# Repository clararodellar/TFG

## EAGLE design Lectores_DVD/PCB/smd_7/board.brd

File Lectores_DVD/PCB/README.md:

En esta carpeta están los archivos para poder hacer la PCB, tanto el archivo esquemático (.sch) como el archivo de la placa (.brd).

Estas placas están hechas para que la conexión de los componentes a Arduino sea más cómoda.

Los componentes tienen las siguientes librerías: 52793-xx70, siendo xx el número de pines que tiene el conector.

Todos estos conectores sirven para conectar los motores de los lectores de DVD y hacemos la conexión a Arduino para poder comprobarlos.

La forma en que están nombrados es smd por su forma de conexión a la placa y el número en función del número de pines que tenga.

A continuación adjunto una imagen de los componentes de una de las disqueteras.

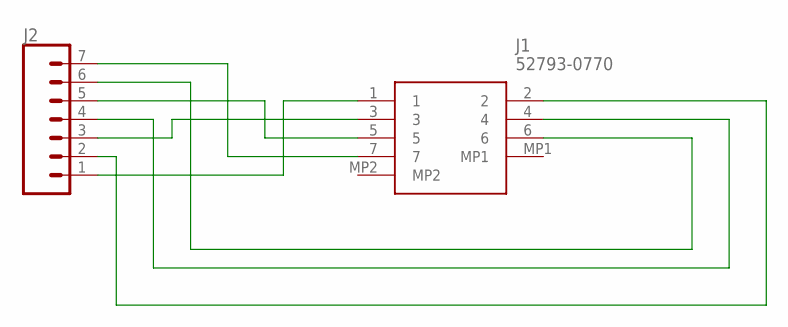
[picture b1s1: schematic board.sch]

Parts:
J1: 52793-0770; 527930770
J2: CONN_07; 1X07

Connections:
unnamed: J1.1, J2.1
unnamed: J1.2, J2.2
unnamed: J1.3, J2.3
unnamed: J1.4, J2.4
unnamed: J1.5, J2.5
unnamed: J1.6, J2.6
unnamed: J1.7, J2.7

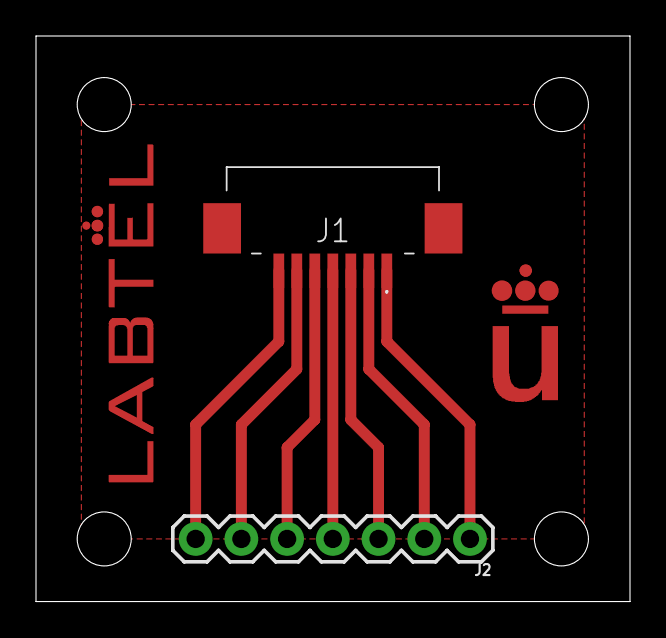
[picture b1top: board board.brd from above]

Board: 2 copper layers, 33.0 x 31.4 mm, 4 parts (0 on the bottom side), 7 nets.

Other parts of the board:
U$1: URJC
U$2: LABTEL

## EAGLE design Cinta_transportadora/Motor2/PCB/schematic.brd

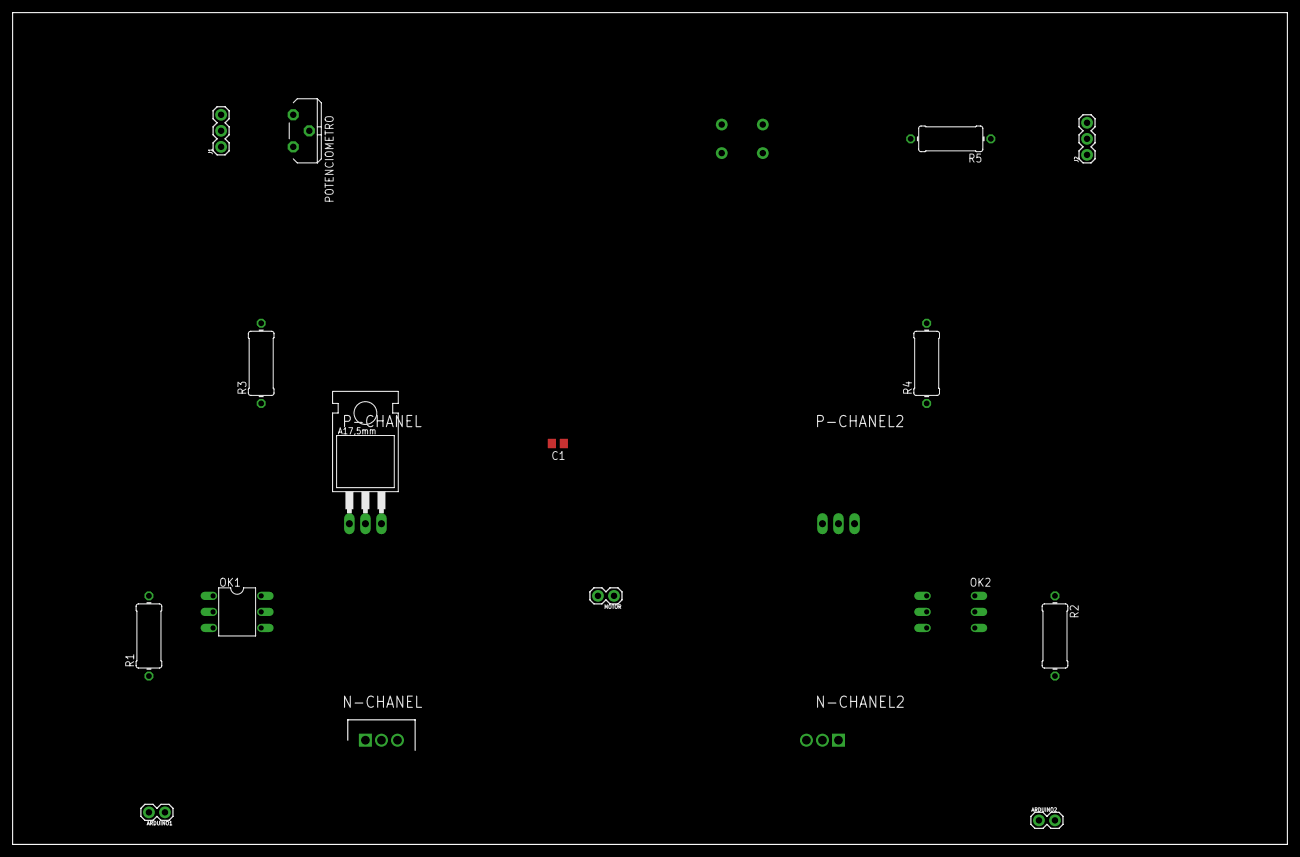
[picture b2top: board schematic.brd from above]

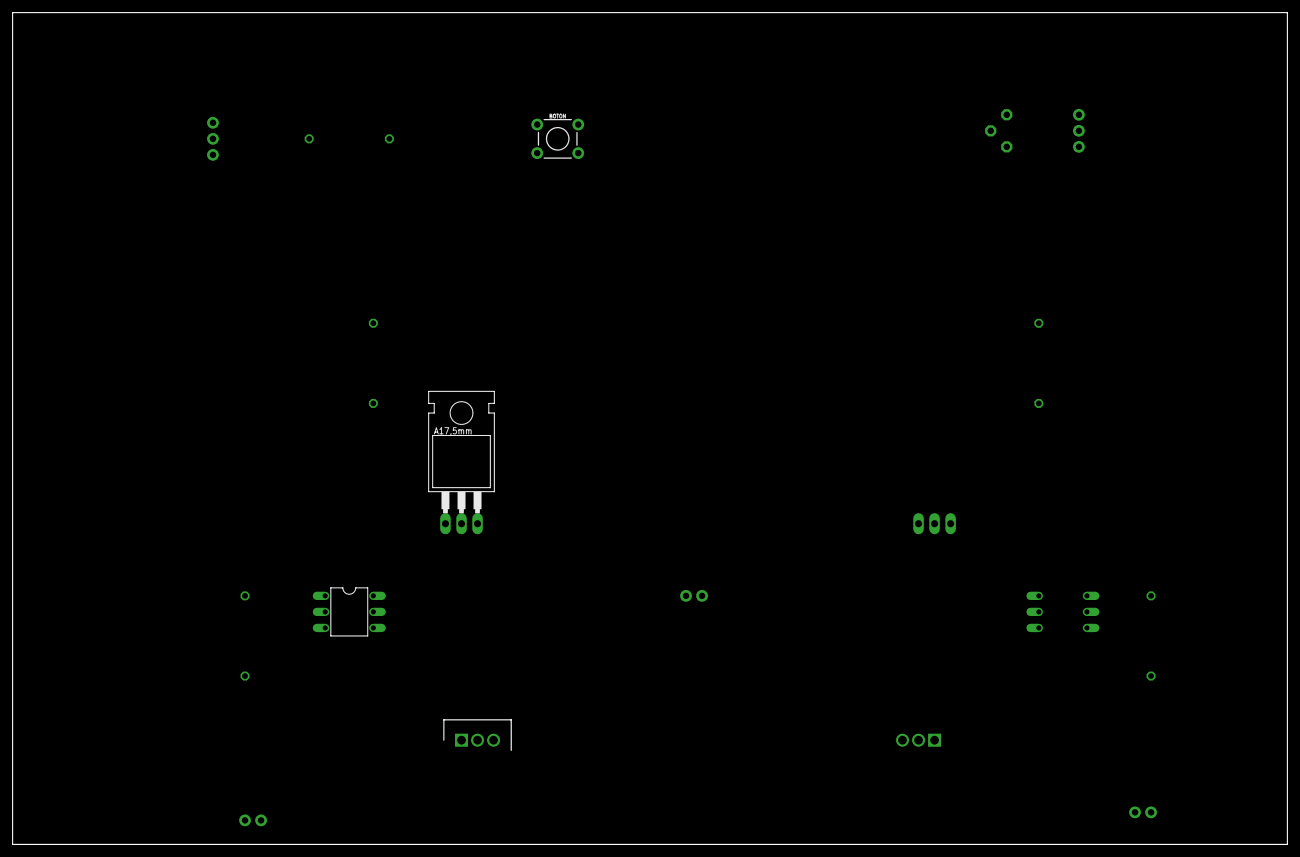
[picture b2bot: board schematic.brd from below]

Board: 2 copper layers, 201.9 x 131.8 mm, 19 parts (4 on the bottom side), 18 nets, no tracks yet.

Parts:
ARDUINO1, ARDUINO2: 1X02
BOTON: MOMENTARY-SWITCH-SPST-PTH-6.0MM; TACTILE_SWITCH_PTH_6.0MM
C1: C0805
J1, J2: 455-1750-1-ND; 1X03
MOTOR: 1X02
N-CHANEL, N-CHANEL2: IRLB8721PBF; TO254P483X1016X1994-3P
OK1, OK2: 4N35; DIL06
P-CHANEL, P-CHANEL2: FQP27P06; TO220
POTENCIOMETRO: PT-10S
R1, R2: 330 ohm; 0411/12
R3, R4: 1 k; 0411/12
R5: 0411/12

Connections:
5V: C1.1, P-CHANEL.3, P-CHANEL2.3, R3.2, R4.2
GND: C1.2, N-CHANEL.3, N-CHANEL2.3, OK1.4, OK2.4
unnamed: MOTOR.2, N-CHANEL.2, P-CHANEL.2
unnamed: MOTOR.1, N-CHANEL2.2, P-CHANEL2.2
unnamed: N-CHANEL2.1, OK2.5, P-CHANEL2.1, R4.1
unnamed: OK1.1, R1.2
unnamed: N-CHANEL.1, OK1.5, P-CHANEL.1, R3.1
unnamed: ARDUINO1.2, R1.1
unnamed: ARDUINO1.1, OK1.2
unnamed: OK2.1, R2.1
unnamed: ARDUINO2.2, R2.2
unnamed: ARDUINO2.1, OK2.2
unnamed: J2.2, R5.1
unnamed: J1.3, POTENCIOMETRO.1
unnamed: J1.2, POTENCIOMETRO.3
unnamed: J1.1, POTENCIOMETRO.2
unnamed: BOTON.1, J2.3, R5.2
unnamed: BOTON.3, J2.1

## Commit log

2018-09-25 Carpetas
2018-09-28 elimino archivos repetidos
2018-09-30 Add datasheets
2018-10-02 Add stl
2018-10-06 Add ULN2003 datasheet
2018-10-11 Add datasheets and link to circuit
2018-10-20 Add uln2803 datasheet
2018-10-25 novedades
2018-10-25 nuevo
2018-10-25 imagen
2018-10-25 imagen2
2018-10-25 codigo_motor
2018-10-25 agarradera-modificada
2018-11-06 conexiones_motor
2018-11-06 ver_foto
2018-11-16 Add some datasheets
2018-11-25 actualizar_readme
2018-11-25 codigo_motor_puenteH
2018-11-25 readme_codigo
2018-11-25 readme_
2018-11-25 actualizar_readme_codigo
2018-11-26 piezas_nuevas
2018-11-26 piezas_imprimir
2018-11-28 Add stepper datasheet
2019-02-16 Actualilzacion
2019-02-16 lectores-dvd
2019-02-16 actualizar
2019-02-16 eliminar
2019-02-16 actualizacion
2019-02-16 actualizacion_README
2019-03-04 Actualizar readme
2019-03-06 Componente_insercion
2019-09-11 elimino carpeta para reorganizar
2019-09-11 elimino la carpeta para reorganizar
2019-09-11 incluir datasheets
2019-09-11 Electronica de control
2019-09-11 Electronica de potencia
2019-09-11 Fotos
2019-09-11 Mecanica
2019-09-11 readme
2019-09-13 nuevos codigos
2019-10-11 memoria
2019-10-11 transistor

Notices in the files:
parts and their libraries:
SparkFun-Connectors: Licensing: Creative Commons ShareAlike 4.0 International - https://creativecommons.org/licenses/by-sa/4.0
